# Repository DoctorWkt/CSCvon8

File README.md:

# CSCvon8: 8-bit von Neumann Crazy Small CPU

This repository holds the files for my 8-bit "big brother" CPU to the
[4-bit Crazy Small CPU](https://minnie.tuhs.org/Programs/CrazySmallCPU/).
This is a von Neumann style CPU designed with 7400-style logic chips, 32K of RAM, 32K of ROM and a UART. The CPU requires only seventeen chips, not including the
clock circuitry.
A short video is [here](https://www.youtube.com/watch?v=LJe3Z_fGDhg).

The overall design of the CPU is covered in
[Docs/CSCvon8_design.md](Docs/CSCvon8_design.md). Also read the
[getting started guide](Docs/getgoing_instructions.md) and the
[guide to building the PCB version](Docs/building_the_CSCvon8.md).

As at the 18th May 2019 I have the CPU running solidly at 3.57MHz on
the PCBs that I ordered from the PCB design in the Schematics folder.
I've kept a [journal](journal.md) with details of my progress from the
initial design phase through to the successful build.

The files and folders in this repository are:
- *Docs*, documents on the design and how to use the tools below
- *Examples*, example programs for the CPU
- *Schematic*, a KiCad schematic of the CPU
- *cas*, the assembler for the CPU
- *clc*, a very crude compiler that outputs assembly that can be given to cas
- *csim*, a simulator of the CPU written in Perl
- *disasm*, a tool to disassemble the instruction ROM contents
- *gen_alu*, a program to generate the contents of the ALU ROM
- *gen_ucode*, a program to generate the contents of the Decode ROM
- *journal.txt*, my running journal of the design and implementation of CSCvon8

There is also a Verilog version with the top-level file being
*ttlcsvon8.v*, the testbench is *icarus_tb.v* and the *Makefile* will
build and run the Verilog testbench. Some notes on this implementation
are in the
[*Docs/implementation_notes.md*](Docs/implementation_notes.md) file.

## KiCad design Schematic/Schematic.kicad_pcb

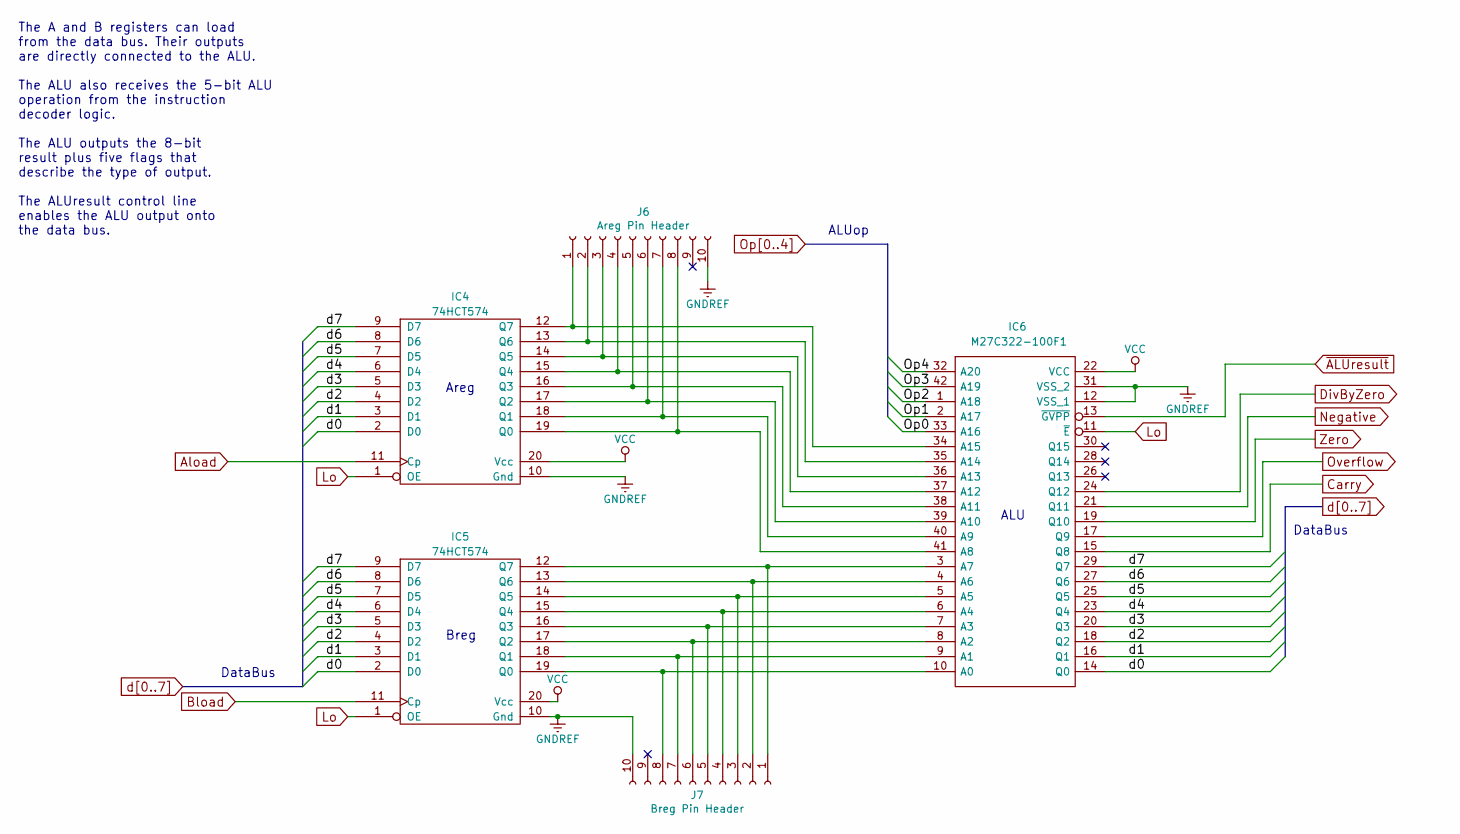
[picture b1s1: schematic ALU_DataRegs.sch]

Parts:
IC4, IC5: 74HCT574; DIP-20_W7.62mm_Socket
IC6: M27C322-100F1; DIP-42_W15.24mm_Socket; Manufacturer_Part_Number M27C322-100F1; Mouser Part Number 511-M27C322-10F
J6: Areg Pin Header; PinSocket_1x10_P2.54mm_Vertical
J7: Breg Pin Header; PinSocket_1x10_P2.54mm_Vertical

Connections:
Aload: IC4.11 (Cp); also elsewhere on the board
Bload: IC5.11 (Cp); also elsewhere on the board
Carry: IC6.15 (Q8); also elsewhere on the board
DivByZero: IC6.24 (Q12); also elsewhere on the board
Hi: IC4.20 (Vcc), IC5.20 (Vcc), IC6.22 (VCC); also elsewhere on the board
Negative: IC6.21 (Q11); also elsewhere on the board
unnamed: IC4.12 (Q7), IC6.34 (A15), J6.1
unnamed: IC4.13 (Q6), IC6.35 (A14), J6.2
unnamed: IC4.14 (Q5), IC6.36 (A13), J6.3
unnamed: IC4.15 (Q4), IC6.37 (A12), J6.4
unnamed: IC4.16 (Q3), IC6.38 (A11), J6.5
unnamed: IC4.17 (Q2), IC6.39 (A10), J6.6
unnamed: IC4.18 (Q1), IC6.40 (A9), J6.7
unnamed: IC4.19 (Q0), IC6.41 (A8), J6.8
unnamed: IC5.12 (Q7), IC6.3 (A7), J7.1
unnamed: IC5.13 (Q6), IC6.4 (A6), J7.2
unnamed: IC5.14 (Q5), IC6.5 (A5), J7.3
unnamed: IC5.15 (Q4), IC6.6 (A4), J7.4
unnamed: IC5.16 (Q3), IC6.7 (A3), J7.5
unnamed: IC5.17 (Q2), IC6.8 (A2), J7.6
unnamed: IC5.18 (Q1), IC6.9 (A1), J7.7
unnamed: IC5.19 (Q0), IC6.10 (A0), J7.8
Op0: IC6.33 (A16); also elsewhere on the board
Op1: IC6.2 (A17); also elsewhere on the board
Op2: IC6.1 (A18); also elsewhere on the board
Op3: IC6.42 (A19); also elsewhere on the board
Op4: IC6.32 (A20); also elsewhere on the board
Overflow: IC6.17 (Q9); also elsewhere on the board
Zero: IC6.19 (Q10); also elsewhere on the board
d0: IC4.2 (D0), IC5.2 (D0), IC6.14 (Q0); also elsewhere on the board
d1: IC4.3 (D1), IC5.3 (D1), IC6.16 (Q1); also elsewhere on the board
d2: IC4.4 (D2), IC5.4 (D2), IC6.18 (Q2); also elsewhere on the board
d3: IC4.5 (D3), IC5.5 (D3), IC6.20 (Q3); also elsewhere on the board
d4: IC4.6 (D4), IC5.6 (D4), IC6.23 (Q4); also elsewhere on the board
d5: IC4.7 (D5), IC5.7 (D5), IC6.25 (Q5); also elsewhere on the board
d6: IC4.8 (D6), IC5.8 (D6), IC6.27 (Q6); also elsewhere on the board
d7: IC4.9 (D7), IC5.9 (D7), IC6.29 (Q7); also elsewhere on the board
~ALUresult: IC6.13 (~GVPP); also elsewhere on the board

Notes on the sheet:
ALU
Areg
Breg
DataBus
ALUop
The A and B registers can load from the data bus. Their outputs are directly connected to the ALU. The ALU also receives the 5-bit ALU operation from the instruction decoder logic. The ALU outputs the 8-bit result plus five flags that describe the type of output. The ALUresult control line enables 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

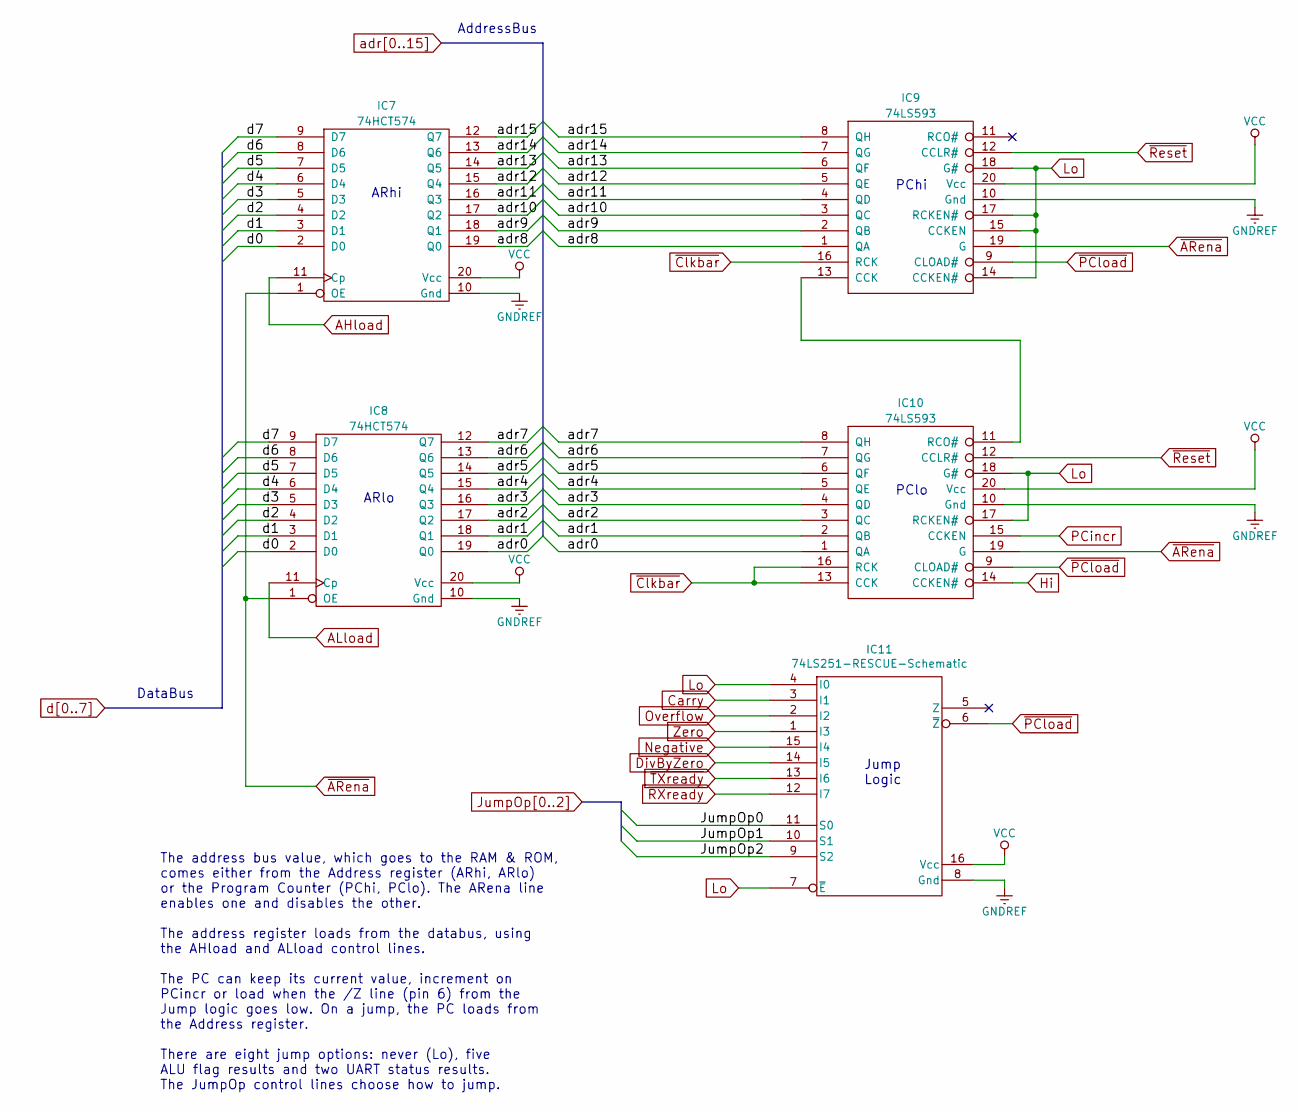
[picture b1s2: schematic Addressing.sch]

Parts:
IC7, IC8: 74HCT574; DIP-20_W7.62mm_Socket
IC9, IC10: 74LS593; DIP-20_W7.62mm_Socket
IC11: 74LS251-RESCUE-Schematic; DIP-16_W7.62mm_Socket

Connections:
AHload: IC7.11 (Cp); also elsewhere on the board
ALload: IC8.11 (Cp); also elsewhere on the board
Carry: IC11.3 (I1); also elsewhere on the board
DivByZero: IC11.14 (I5); also elsewhere on the board
Hi: IC7.20 (Vcc), IC8.20 (Vcc), IC9.20 (Vcc), IC10.14 (CCKEN#), IC10.20 (Vcc), IC11.16 (Vcc); also elsewhere on the board
JumpOp0: IC11.11 (S0); also elsewhere on the board
JumpOp1: IC11.10 (S1); also elsewhere on the board
JumpOp2: IC11.9 (S2); also elsewhere on the board
Negative: IC11.15 (I4); also elsewhere on the board
unnamed: IC9.13 (CCK), IC10.11 (RCO#)
Overflow: IC11.2 (I2); also elsewhere on the board
PCincr: IC10.15 (CCKEN); also elsewhere on the board
Zero: IC11.1 (I3); also elsewhere on the board
adr0: IC8.19 (Q0), IC10.1 (QA); also elsewhere on the board
adr1: IC8.18 (Q1), IC10.2 (QB); also elsewhere on the board
adr2: IC8.17 (Q2), IC10.3 (QC); also elsewhere on the board
adr3: IC8.16 (Q3), IC10.4 (QD); also elsewhere on the board
adr4: IC8.15 (Q4), IC10.5 (QE); also elsewhere on the board
adr5: IC8.14 (Q5), IC10.6 (QF); also elsewhere on the board
adr6: IC8.13 (Q6), IC10.7 (QG); also elsewhere on the board
adr7: IC8.12 (Q7), IC10.8 (QH); also elsewhere on the board
adr8: IC7.19 (Q0), IC9.1 (QA); also elsewhere on the board
adr9: IC7.18 (Q1), IC9.2 (QB); also elsewhere on the board
adr10: IC7.17 (Q2), IC9.3 (QC); also elsewhere on the board
adr11: IC7.16 (Q3), IC9.4 (QD); also elsewhere on the board
adr12: IC7.15 (Q4), IC9.5 (QE); also elsewhere on the board
adr13: IC7.14 (Q5), IC9.6 (QF); also elsewhere on the board
adr14: IC7.13 (Q6), IC9.7 (QG); also elsewhere on the board
adr15: IC7.12 (Q7), IC9.8 (QH); also elsewhere on the board
d0: IC7.2 (D0), IC8.2 (D0); also elsewhere on the board
d1: IC7.3 (D1), IC8.3 (D1); also elsewhere on the board
d2: IC7.4 (D2), IC8.4 (D2); also elsewhere on the board
d3: IC7.5 (D3), IC8.5 (D3); also elsewhere on the board
d4: IC7.6 (D4), IC8.6 (D4); also elsewhere on the board
d5: IC7.7 (D5), IC8.7 (D5); also elsewhere on the board
d6: IC7.8 (D6), IC8.8 (D6); also elsewhere on the board
d7: IC7.9 (D7), IC8.9 (D7); also elsewhere on the board
~ARena: IC7.1 (OE), IC8.1 (OE), IC9.19 (G), IC10.19 (G); also elsewhere on the board
~Clkbar: IC9.16 (RCK), IC10.13 (CCK), IC10.16 (RCK); also elsewhere on the board
~PCload: IC9.9 (CLOAD#), IC10.9 (CLOAD#), IC11.6 (~Z)
~RXready: IC11.12 (I7); also elsewhere on the board
~Reset: IC9.12 (CCLR#), IC10.12 (CCLR#); also elsewhere on the board
~TXready: IC11.13 (I6); also elsewhere on the board

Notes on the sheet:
Jump Logic
ARhi
ARlo
PChi
PClo
DataBus
AddressBus
The address bus value, which goes to the RAM & ROM, comes either from the Address register (ARhi, ARlo) or the Program Counter (PChi, PClo). The ARena line enables one and disables the other. The address register loads from the databus, using the AHload and ALload control lines. The PC can keep its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

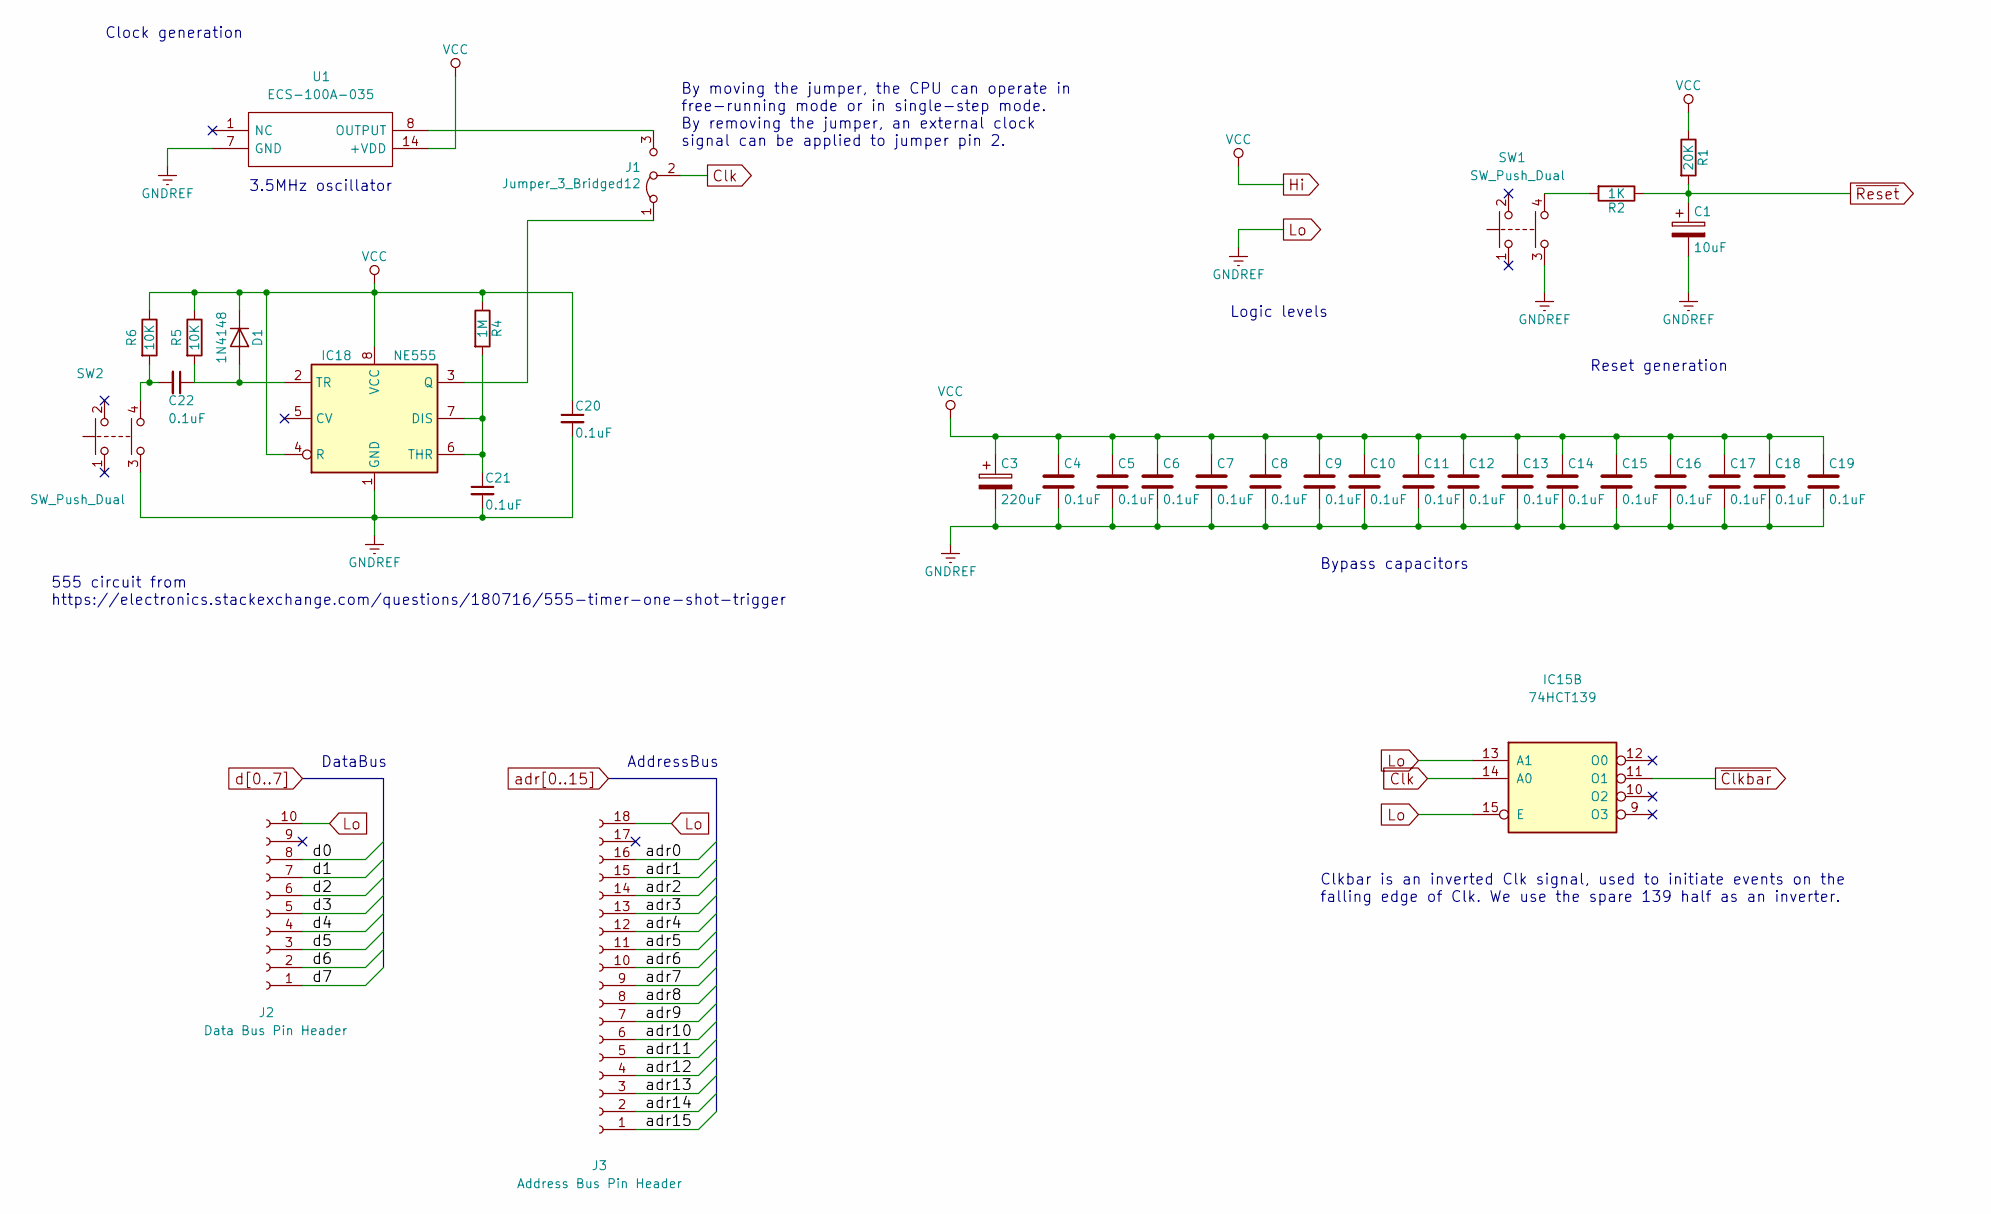
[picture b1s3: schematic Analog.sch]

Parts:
C1: 10uF; CP_Radial_D5.0mm_P2.00mm
C3: 220uF; CP_Radial_D8.0mm_P5.00mm
C4, C5, C6, C7, C8, C9, C10, C11, C12, C13, C14, C15, C16, C17, C18, C19, C20, C21, C22: 0.1uF; C_Disc_D4.7mm_W2.5mm_P5.00mm
D1: 1N4148; D_DO-35_SOD27_P2.54mm_Vertical_AnodeUp
IC15: 74HCT139; DIP-16_W7.62mm_Socket
IC18: NE555; DIP-8_W7.62mm_Socket
J1: Jumper_3_Bridged12; PinSocket_1x03_P2.54mm_Vertical
J2: Data Bus Pin Header; PinSocket_1x10_P2.54mm_Vertical
J3: Address Bus Pin Header; PinSocket_1x18_P2.54mm_Vertical
R1: 20K; R_Axial_DIN0204_L3.6mm_D1.6mm_P1.90mm_Vertical
R2: 1K; R_Axial_DIN0204_L3.6mm_D1.6mm_P1.90mm_Vertical
R4: 1M; R_Axial_DIN0204_L3.6mm_D1.6mm_P1.90mm_Vertical
R5, R6: 10K; R_Axial_DIN0204_L3.6mm_D1.6mm_P1.90mm_Vertical
SW1, SW2: SW_Push_Dual; Push_E-Switch_KS01Q01
U1: ECS-100A-035; QX14T50B1.843200B50TT; Manufacturer_Part_Number QX14T50B1.843200B50TT

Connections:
/Instruction Decode/DbusOp0: IC15.2 (A0); also elsewhere on the board
/Instruction Decode/DbusOp1: IC15.3 (A1); also elsewhere on the board
Hi: C3.1, C4.1, C5.1, C6.1, C7.1, C8.1, C9.1, C10.1, C11.1, C12.1, C13.1, C14.1, C15.1, C16.1, C17.1, C18.1, C19.1, C20.1, D1.1 (K), IC15.16 (VCC), IC18.4 (R), IC18.8 (VCC), R1.1, R4.1, R5.1, R6.1, U1.14 (+VDD); also elsewhere on the board
unnamed: C21.1, IC18.6 (THR), IC18.7 (DIS), R4.2
unnamed: C22.1, D1.2 (A), IC18.2 (TR), R5.2
unnamed: C22.2, R6.2, SW2.4
unnamed: IC18.3 (Q), J1.1 (A)
unnamed: J1.3 (B), U1.8 (OUTPUT)
unnamed: R2.2, SW1.4
adr0: J3.16; also elsewhere on the board
adr1: J3.15; also elsewhere on the board
adr2: J3.14; also elsewhere on the board
adr3: J3.13; also elsewhere on the board
adr4: J3.12; also elsewhere on the board
adr5: J3.11; also elsewhere on the board
adr6: J3.10; also elsewhere on the board
adr7: J3.9; also elsewhere on the board
adr8: J3.8; also elsewhere on the board
adr9: J3.7; also elsewhere on the board
adr10: J3.6; also elsewhere on the board
adr11: J3.5; also elsewhere on the board
adr12: J3.4; also elsewhere on the board
adr13: J3.3; also elsewhere on the board
adr14: J3.2; also elsewhere on the board
adr15: J3.1; also elsewhere on the board
d0: J2.8; also elsewhere on the board
d1: J2.7; also elsewhere on the board
d2: J2.6; also elsewhere on the board
d3: J2.5; also elsewhere on the board
d4: J2.4; also elsewhere on the board
d5: J2.3; also elsewhere on the board
d6: J2.2; also elsewhere on the board
d7: J2.1; also elsewhere on the board
~ALUresult: IC15.5 (O1); also elsewhere on the board
~Clkbar: IC15.11 (O1); also elsewhere on the board
~MEMresult: IC15.4 (O0); also elsewhere on the board
~Reset: C1.1, R1.2, R2.1; also elsewhere on the board
~UARTresult: IC15.6 (O2); also elsewhere on the board

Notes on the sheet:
By moving the jumper, the CPU can operate in free-running mode or in single-step mode. By removing the jumper, an external clock signal can be applied to jumper pin 2.
3.5MHz oscillator
Bypass capacitors
Reset generation
Clock generation
Logic levels
DataBus
AddressBus
555 circuit from https://electronics.stackexchange.com/questions/180716/555-timer-one-shot-trigger
Clkbar is an inverted Clk signal, used to initiate events on the falling edge of Clk. We use the spare 139 half as an inverter.

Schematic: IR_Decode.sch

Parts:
IC12: 74HCT574; DIP-20_W7.62mm_Socket
IC13: 74HCT161; DIP-16_W7.62mm_Socket
IC14: AT27C1024-70PU; DIP-40_W15.24mm_Socket; Manufacturer_Part_Number AT27C1024-70PU; Mouser Part Number 556-AT27C102470PU
IC15: 74HCT139; DIP-16_W7.62mm_Socket
IC16: 74HCT138; DIP-16_W7.62mm_Socket
IC17: 74LS04; DIP-14_W7.62mm_Socket
J4: uSeq Pin Header; Socket_Strip_Straight_1x06_Pitch2.54mm
J5: IR Pin Header; Socket_Strip_Straight_1x10_Pitch2.54mm

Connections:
/Instruction Decode/DbusOp0: IC14.10, IC15.2 (A0)
/Instruction Decode/DbusOp1: IC14.9, IC15.3 (A1)
/Instruction Decode/LoadOp0: IC14.14, IC16.1
/Instruction Decode/LoadOp1: IC14.13, IC16.2
/Instruction Decode/LoadOp2: IC14.12, IC16.3
AHload: IC17.8; also elsewhere on the board
ALload: IC17.10; also elsewhere on the board
Aload: IC17.4; also elsewhere on the board
Bload: IC17.6; also elsewhere on the board
Hi: IC12.20, IC13.7, IC13.10, IC13.16, IC14.1, IC14.39, IC14.40, IC15.16 (VCC), IC16.6, IC16.16, IC17.14 (VCC); also elsewhere on the board
IRload: IC12.11, IC17.2
JumpOp0: IC14.8; also elsewhere on the board
JumpOp1: IC14.7; also elsewhere on the board
JumpOp2: IC14.6; also elsewhere on the board
unnamed: IC12.12, IC14.33, J5.1
unnamed: IC12.13, IC14.32, J5.2
unnamed: IC12.14, IC14.31, J5.3
unnamed: IC12.15, IC14.29, J5.4
unnamed: IC12.16, IC14.28, J5.5
unnamed: IC12.17, IC14.27, J5.6
unnamed: IC12.18, IC14.26, J5.7
unnamed: IC12.19, IC14.25, J5.8
unnamed: IC13.11, IC14.24, J4.1
unnamed: IC13.12, IC14.23, J4.2
unnamed: IC13.13, IC14.22, J4.3
unnamed: IC13.14, IC14.21, J4.4
unnamed: IC16.9, IC17.11
unnamed: IC16.10, IC17.9
unnamed: IC16.12, IC17.5
unnamed: IC16.13, IC17.3
unnamed: IC16.14, IC17.1
Op0: IC14.19; also elsewhere on the board
Op1: IC14.18; also elsewhere on the board
Op2: IC14.17; also elsewhere on the board
Op3: IC14.16; also elsewhere on the board
Op4: IC14.15; also elsewhere on the board
PCincr: IC14.4; also elsewhere on the board
d0: IC12.2; also elsewhere on the board
d1: IC12.3; also elsewhere on the board
d2: IC12.4; also elsewhere on the board
d3: IC12.5; also elsewhere on the board
d4: IC12.6; also elsewhere on the board
d5: IC12.7; also elsewhere on the board
d6: IC12.8; also elsewhere on the board
d7: IC12.9; also elsewhere on the board
~ALUresult: IC15.5 (O1); also elsewhere on the board
~ARena: IC14.5; also elsewhere on the board
~IOload: IC16.7; also elsewhere on the board
~MEMload: IC16.11; also elsewhere on the board
~MEMresult: IC15.4 (O0); also elsewhere on the board
~Reset: IC13.1; also elsewhere on the board
~UARTresult: IC15.6 (O2); also elsewhere on the board
~uSreset: IC13.9, IC14.3

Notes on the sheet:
Decode ROM
uSequence Counter
Databus Writer demux
Databus Reader demux
DataBus
ALUop
CSCvon8 is a microsequenced CPU. The Instruction register, combined with the microsequence counter, selects the next microinstruction to perform. This is "looked up" in the Decode ROM, which produces the sixteen control lines for the specific microinstruction. The ALUop goes to the ALU. The JumpOp 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
It's so annoying that the 74HCT574 has an active high load line, and the RAM and UART have active low load lines. One extra chip just to deal with that, sigh.

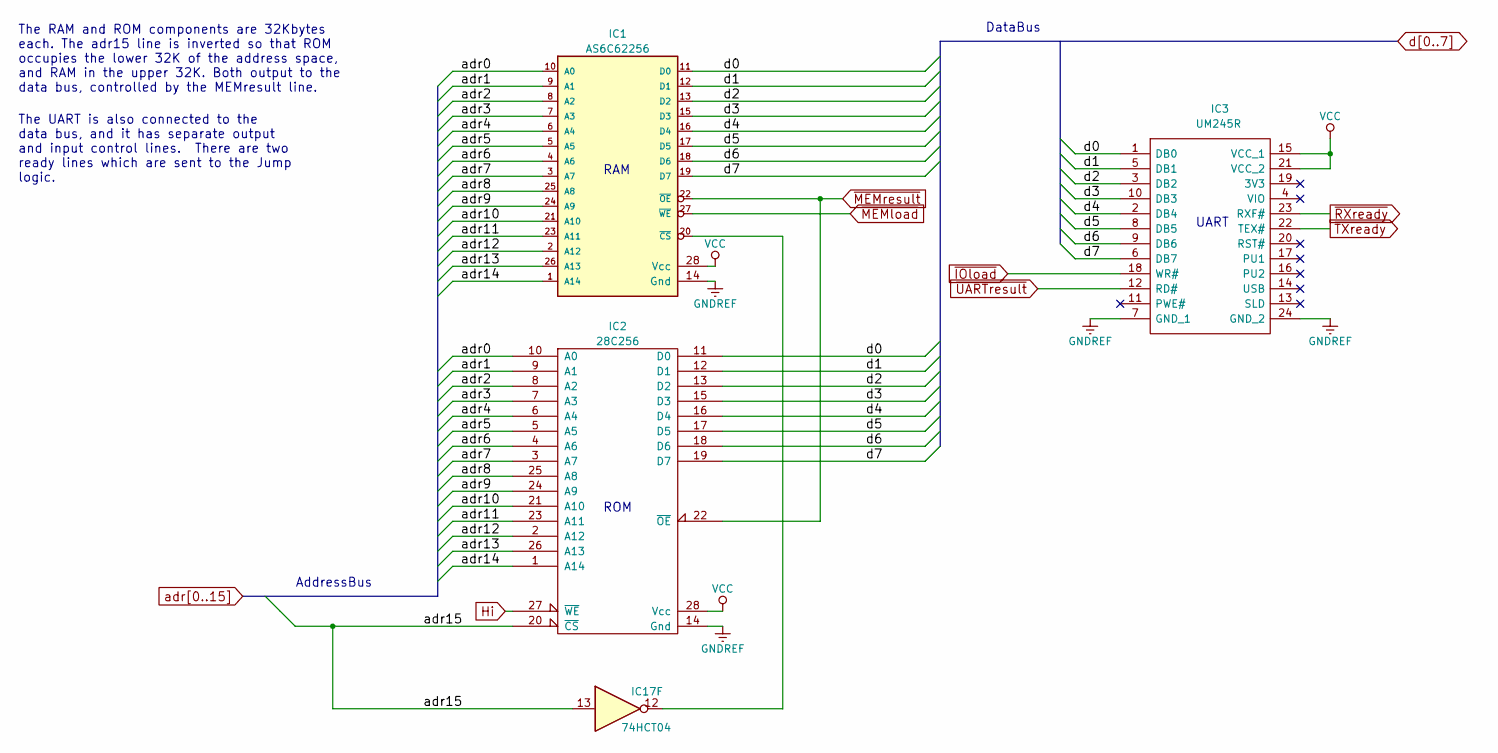
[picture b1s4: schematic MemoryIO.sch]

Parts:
IC1: AS6C62256; DIP-28_W15.24mm_Socket
IC2: 28C256; DIP-28_W15.24mm_Socket
IC3: UM245R; DIP-24_W15.24mm_Socket; Manufacturer_Part_Number UM245R; Mouser Part Number 895-UM245R
IC17: 74HCT04; DIP-14_W7.62mm_Socket

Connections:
AHload: IC17.8; also elsewhere on the board
ALload: IC17.10; also elsewhere on the board
Aload: IC17.4; also elsewhere on the board
Bload: IC17.6; also elsewhere on the board
Hi: IC1.28 (Vcc), IC2.27 (~WE), IC2.28 (Vcc), IC3.15 (VCC_1), IC3.21 (VCC_2), IC17.14 (VCC); also elsewhere on the board
IRload: IC17.2; also elsewhere on the board
unnamed: IC1.20 (~CS), IC17.12
unnamed 69: IC17.11; also elsewhere on the board
unnamed 70: IC17.9; also elsewhere on the board
unnamed 71: IC17.5; also elsewhere on the board
unnamed 72: IC17.3; also elsewhere on the board
unnamed 73: IC17.1; also elsewhere on the board
adr0: IC1.10 (A0), IC2.10 (A0); also elsewhere on the board
adr1: IC1.9 (A1), IC2.9 (A1); also elsewhere on the board
adr2: IC1.8 (A2), IC2.8 (A2); also elsewhere on the board
adr3: IC1.7 (A3), IC2.7 (A3); also elsewhere on the board
adr4: IC1.6 (A4), IC2.6 (A4); also elsewhere on the board
adr5: IC1.5 (A5), IC2.5 (A5); also elsewhere on the board
adr6: IC1.4 (A6), IC2.4 (A6); also elsewhere on the board
adr7: IC1.3 (A7), IC2.3 (A7); also elsewhere on the board
adr8: IC1.25 (A8), IC2.25 (A8); also elsewhere on the board
adr9: IC1.24 (A9), IC2.24 (A9); also elsewhere on the board
adr10: IC1.21 (A10), IC2.21 (A10); also elsewhere on the board
adr11: IC1.23 (A11), IC2.23 (A11); also elsewhere on the board
adr12: IC1.2 (A12), IC2.2 (A12); also elsewhere on the board
adr13: IC1.26 (A13), IC2.26 (A13); also elsewhere on the board
adr14: IC1.1 (A14), IC2.1 (A14); also elsewhere on the board
adr15: IC2.20 (~CS), IC17.13; also elsewhere on the board
d0: IC1.11 (D0), IC2.11 (D0), IC3.1 (DB0); also elsewhere on the board
d1: IC1.12 (D1), IC2.12 (D1), IC3.5 (DB1); also elsewhere on the board
d2: IC1.13 (D2), IC2.13 (D2), IC3.3 (DB2); also elsewhere on the board
d3: IC1.15 (D3), IC2.15 (D3), IC3.10 (DB3); also elsewhere on the board
d4: IC1.16 (D4), IC2.16 (D4), IC3.2 (DB4); also elsewhere on the board
d5: IC1.17 (D5), IC2.17 (D5), IC3.8 (DB5); also elsewhere on the board
d6: IC1.18 (D6), IC2.18 (D6), IC3.9 (DB6); also elsewhere on the board
d7: IC1.19 (D7), IC2.19 (D7), IC3.6 (DB7); also elsewhere on the board
~IOload: IC3.18 (WR#); also elsewhere on the board
~MEMload: IC1.27 (~WE); also elsewhere on the board
~MEMresult: IC1.22 (~OE), IC2.22 (~OE); also elsewhere on the board
~RXready: IC3.23 (RXF#); also elsewhere on the board
~TXready: IC3.22 (TEX#); also elsewhere on the board
~UARTresult: IC3.12 (RD#); also elsewhere on the board

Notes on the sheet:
RAM
ROM
UART
AddressBus
DataBus
The RAM and ROM components are 32Kbytes each. The adr15 line is inverted so that ROM occupies the lower 32K of the address space, and RAM in the upper 32K. Both output to the data bus, controlled by the MEMresult line.
The UART is also connected to the data bus, and it has separate output and input control lines. There are two ready lines which are sent to the Jump logic.

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
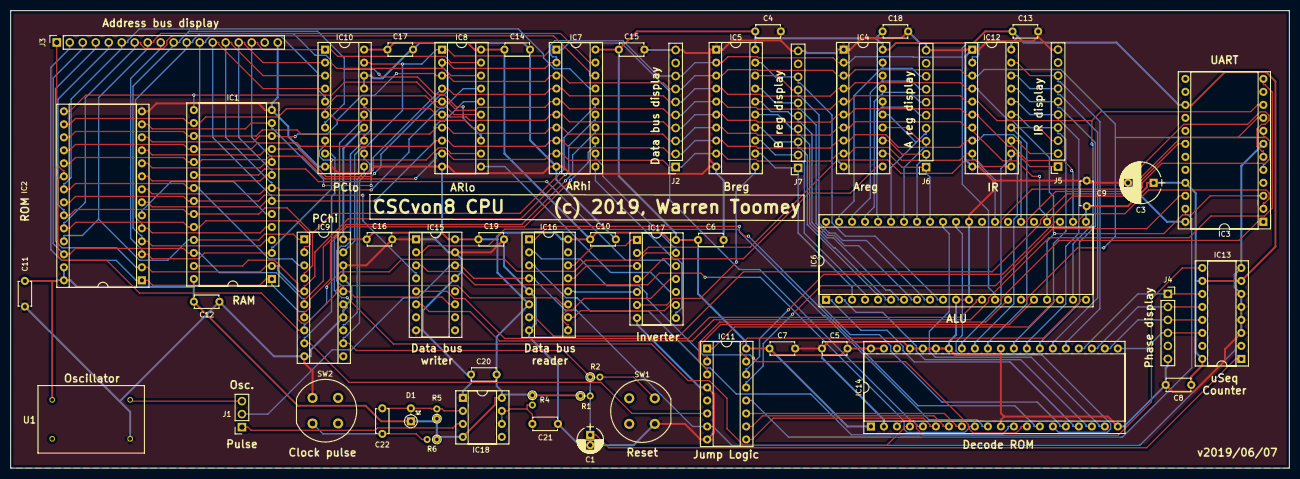
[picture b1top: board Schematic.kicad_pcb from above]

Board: 2 copper layers, 249.9 x 89.4 mm, 55 parts (0 on the bottom side), 104 nets.

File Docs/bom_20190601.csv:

Source:,/home/wkt/ownCloud/CSCvon8/Schematic/Schematic.sch,
Date:,Thu 09 May 2019 13:39:52 AEST,
Tool:,Eeschema 5.1.2-f72e74a~84~ubuntu18.04.1,
Component Count:,55,
,,
Ref,Value,Footprint
C1,10uF,Capacitors_THT:CP_Radial_D5.0mm_P2.00mm
C3,220uF,Capacitors_THT:CP_Radial_D8.0mm_P5.00mm
C4,0.1uF,Capacitors_THT:C_Disc_D4.7mm_W2.5mm_P5.00mm
C5,0.1uF,Capacitors_THT:C_Disc_D4.7mm_W2.5mm_P5.00mm
C6,0.1uF,Capacitors_THT:C_Disc_D4.7mm_W2.5mm_P5.00mm
C7,0.1uF,Capacitors_THT:C_Disc_D4.7mm_W2.5mm_P5.00mm
C8,0.1uF,Capacitors_THT:C_Disc_D4.7mm_W2.5mm_P5.00mm
C9,0.1uF,Capacitors_THT:C_Disc_D4.7mm_W2.5mm_P5.00mm
C10,0.1uF,Capacitors_THT:C_Disc_D4.7mm_W2.5mm_P5.00mm
C11,0.1uF,Capacitors_THT:C_Disc_D4.7mm_W2.5mm_P5.00mm
C12,0.1uF,Capacitors_THT:C_Disc_D4.7mm_W2.5mm_P5.00mm
C13,0.1uF,Capacitors_THT:C_Disc_D4.7mm_W2.5mm_P5.00mm
C14,0.1uF,Capacitors_THT:C_Disc_D4.7mm_W2.5mm_P5.00mm
C15,0.1uF,Capacitors_THT:C_Disc_D4.7mm_W2.5mm_P5.00mm
C16,0.1uF,Capacitors_THT:C_Disc_D4.7mm_W2.5mm_P5.00mm
C17,0.1uF,Capacitors_THT:C_Disc_D4.7mm_W2.5mm_P5.00mm
C18,0.1uF,Capacitors_THT:C_Disc_D4.7mm_W2.5mm_P5.00mm
C19,0.1uF,Capacitors_THT:C_Disc_D4.7mm_W2.5mm_P5.00mm
C20,0.1uF,Capacitors_THT:C_Disc_D4.7mm_W2.5mm_P5.00mm
C21,0.1uF,Capacitors_THT:C_Disc_D4.7mm_W2.5mm_P5.00mm
C22,0.1uF,Capacitors_THT:C_Disc_D4.7mm_W2.5mm_P5.00mm
D1,1N4148,Diodes_THT:D_DO-35_SOD27_P2.54mm_Vertical_AnodeUp
IC1,AS6C62256,Housings_DIP:DIP-28_W15.24mm_Socket
IC2,28C256,Housings_DIP:DIP-28_W15.24mm_Socket
IC3,UM245R,Housings_DIP:DIP-24_W15.24mm_Socket
IC4,74HCT574,Housings_DIP:DIP-20_W7.62mm_Socket
IC5,74HCT574,Housings_DIP:DIP-20_W7.62mm_Socket
IC6,M27C322-100F1,Housings_DIP:DIP-42_W15.24mm_Socket
IC7,74HCT574,Housings_DIP:DIP-20_W7.62mm_Socket
IC8,74HCT574,Housings_DIP:DIP-20_W7.62mm_Socket
IC9,74LS593,Housings_DIP:DIP-20_W7.62mm_Socket
IC10,74LS593,Housings_DIP:DIP-20_W7.62mm_Socket
IC11,74HCT151,Package_DIP:DIP-16_W7.62mm_Socket
IC12,74HCT574,Housings_DIP:DIP-20_W7.62mm_Socket
IC13,74HCT161,Housings_DIP:DIP-16_W7.62mm_Socket
IC14,AT27C1024-70PU,Housings_DIP:DIP-40_W15.24mm_Socket
IC15,74HCT139,Package_DIP:DIP-16_W7.62mm_Socket
IC16,74HCT138,Housings_DIP:DIP-16_W7.62mm_Socket
IC17,74HCT04,Housings_DIP:DIP-14_W7.62mm_Socket
IC18,NE555,Housings_DIP:DIP-8_W7.62mm_Socket
J1,Jumper_3_Bridged12,Connector_PinSocket_2.54mm:PinSocket_1x03_P2.54mm_Vertical
J2,Data Bus Pin Header,Connector_PinSocket_2.54mm:PinSocket_1x10_P2.54mm_Vertical
J3,Address Bus Pin Header,Connector_PinSocket_2.54mm:PinSocket_1x18_P2.54mm_Vertical
J4,uSeq Pin Header,Connector_PinSocket_2.54mm:PinSocket_1x06_P2.54mm_Vertical
J5,IR Pin Header,Connector_PinSocket_2.54mm:PinSocket_1x10_P2.54mm_Vertical
J6,Areg Pin Header,Connector_PinSocket_2.54mm:PinSocket_1x10_P2.54mm_Vertical
J7,Breg Pin Header,Connector_PinSocket_2.54mm:PinSocket_1x10_P2.54mm_Vertical
R1,20K,Resistors_THT:R_Axial_DIN0204_L3.6mm_D1.6mm_P1.90mm_Vertical
R2,1K,Resistors_THT:R_Axial_DIN0204_L3.6mm_D1.6mm_P1.90mm_Vertical
R4,1M,Resistors_THT:R_Axial_DIN0204_L3.6mm_D1.6mm_P1.90mm_Vertical
R5,10K,Resistors_THT:R_Axial_DIN0204_L3.6mm_D1.6mm_P1.90mm_Vertical
R6,10K,Resistors_THT:R_Axial_DIN0204_L3.6mm_D1.6mm_P1.90mm_Vertical
SW1,SW_Push_Dual,Buttons_Switches_THT:Push_E-Switch_KS01Q01
SW2,SW_Push_Dual,Buttons_Switches_THT:Push_E-Switch_KS01Q01
U1,ECS-100A-035,QX14T50B1.843200B50TT:QX14T50B1.843200B50TT

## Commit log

2019-03-27 First version ready for exposure on Github.
2019-03-27 Broken link in README
2019-03-27 Oops, missed one Verilog source file
2019-03-27 Fixed up some schematic DCN mistakes and also a few minor typos and diagram issues.
2019-03-27 Generated a new schematic of the circuit
2019-03-27 Brought design document up to date with new order of ALU flags lines.
2019-03-27 Working on the PCB
2019-03-28 Added a reset circuit and a single-step clock circuit to the schematic, as well as the bypass capacitors. Also, got used to the PCB creation workflow.
2019-03-28 Brought in support for Verilator
2019-04-23 Brought the schematic and PCB board design up to date.
2019-04-23 Added the Verilog version of the CPU which is composed of models of the TTL components which I will use to build the CPU.
2019-04-23 Tidy up of the docs
2019-04-23 Brought my journal up to date.
2019-04-23 Brought in the new assembler, compiler and other tools that I've been working on.
2019-04-23 Brought the example assembly files up to date with the new assembler.
2019-04-23 Still bringing things up to date. Top Makefile now makes the ALU and microcode ROM contents.
2019-04-23 I've removed the original Verilog version and now have just the TTL Verilog version of the CPU along with the Perl simulator.
2019-04-24 Updated the diagrams of the design.
2019-04-24 Updated the top-level README file
2019-04-24 Updated the get started instructions.
2019-04-24 Updated the design document
2019-04-24 Moved some documentation into the Docs folder.
2019-04-24 Updated the cas assembler manual
2019-04-24 Fixed up some mistakes in the docs.
2019-04-24 Got the CCK enable logic a bit wrong cf. the real chips, so fixed it.
2019-04-25 I missed some control lines to the ROM and then had to fix up a microsequence.
2019-04-25 Brought the schematic up to date with the wiring from the TTL verilog version.
2019-04-25 Moved the Figs into Docs and brought the implementation notes up to date.
2019-04-25 The rewiring of the TTL verilog version has forced an increase in the minimum clock cycle duration.
2019-04-25 Journal entry.
2019-04-25 Going to move the journal to Markdown.
2019-04-25 Got rid of the old text journal.
2019-04-25 More journal notes.
2019-04-25 Updated journal after a bit of a struggle loading the PC.
2019-04-25 More journal entries.
2019-04-26 Updated my 74593 wiring as per my journal notes from last night.
2019-04-26 Reworked the 74LS593 wiring in the KiCad schematic and updated my journal.
2019-04-26 Included a photo of the breadboard in the journal.
2019-04-26 gen_ucode now shows the hex version of each microinstruction with -d
2019-04-26 Updated the PC_circuit.png in the documentation.
2019-04-27 Updated journal, I now have an Instruction ROM and a data bus.
2019-04-28 I wired up some of the A-register and the UART to write from the data bus. I've added an OUT instruction to output the next byte after the instruction byte. I've written a short test program and this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
2019-04-28 Journal update.
2019-04-28 I added a NOP to the start of the example programs, as the hardware doesn't properly run the instruction at $0000 after a reset.
2019-04-28 Fixed some mistakes in the chips and the details of the design.
2019-05-02 Brought the journal up to date
2019-05-02 New image.
2019-05-03 I added the SIA/SIB instructions and had to change a few programs to deal with this. There is an Examples/example10.s program which uses these instructions. Updated the journal too.
2019-05-04 Updated journal.
2019-05-04 Another journal update with a new picture.
2019-05-04 Fixed a bug with the PC incrementing incorrectly.
2019-05-05 I now have a working CPU on the breadboard.
2019-05-05 Journal typos fixed.
2019-05-05 More types fixed!
2019-05-05 Yet another typo corrected.
2019-05-06 Updated the schematic and also moved to KiCad 5.
2019-05-08 Brought the PCB up to date with the new schematic, and tested the RAM with a test program.
2019-05-08 Added -r: randomise RAM to csim, updated my journal.
2019-05-08 I've updated the schematic PDF from the latest KiCad design.
2019-05-08 Updated the PCB image and my journal.
2019-05-09 I forgot the image!
2019-05-09 Typo in journal.
2019-05-09 Updated the README with details of progress.
2019-05-11 Brought the implementation notes up to date with the new PC circuit.
2019-05-13 Some more rewording of the documentation.
2019-05-16 The PCBs have turned up and I'm getting on with the soldering.
2019-05-17 First working instructions on the PCB.
2019-05-17 The PCB is nearly finished, only a few chips left to add. Works so far.
2019-05-17 More journal notes
2019-05-17 A new photo of a working CPU.
2019-05-18 Runs fine a 1MHz.
2019-05-18 Found a workaround to fix the bug in the Jump instructions.
2019-05-18 Improved the microcode and kept the CPU running OK at 3.57MHz.
2019-05-18 Added numeric labels with relative references to the assembler.
2019-05-19 Removed a control line from the microcode to get the LIA and LIB instructions to work on the real hardware.
2019-05-19 Added support for label+num syntax to the assembler.
2019-05-22 Added ; support to cas so I can set up some cpp macros. Updated the journal. I've undone some of the LDA JC style changes because of the side effects of calculating A-1, A+1, B+1 A+B etc. multiple ti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
2019-05-25 I've spent some time shaking out some annoying microcode bugs.
2019-05-25 Added an introduction to the journal.
2019-05-25 Some more updates to the documentation.
2019-05-25 Updated the PCB so that the UM245R has the correct physical orientation with the USB port facing the edge of the PCB.
2019-05-27 I put in a hard-coded UART input value so I can do some sort of INA and INB testing.
2019-05-28 I added support in cas to assemble into RAM and generate a RAM hex file which can be loaded with the monitor.
2019-05-29 I've added one more instruction to the instruction set.
2019-05-30 Added a version of Conway's Game of Life as an example.
2019-05-30 Fix up wktlife.s to clear RAM before it starts.
2019-05-31 Updated the examples to use the current set of instructions.
2019-05-31 Updated the PCB and schematic to have a 330pF capacitor to fix the "jump" glitch that I've been experiencing.
2019-05-31 Brought the journal up to date.
2019-05-31 I finally added the Monitor ROM code, now that it's stable.
2019-05-31 Changed the version number on the PCB to reflect the new capacitor.
2019-05-31 Added a Misc folder in my dev repo.
2019-06-01 I've made a start on a document that describes how to build and test the CSCvon8 CPU on the PCB, in stages.
2019-06-01 I've mostly completed the "building_the_CSCvon8" documentation but there are new small things to add.
2019-06-01 Fixed up some URLs in building_the_CSCvon8.md
2019-06-01 Fixed some more mistakes in building_the_CSCvon8.md
2019-06-01 Added a link to Docs/building_the_CSCvon8.md to the README.
2019-06-01 typo in building_the_CSCvon8.md
2019-06-01 Center the images in building_the_CSCvon8.md
2019-06-01 Removed the centering, didn't work!
2019-06-02 I think I've mostly finished the building_the_CSCvon8.md document except for any typos.
2019-06-02 A better image of the UM245R.
2019-06-02 Found some typos and mistakes in building_the_CSCvon8.md, fixed.
2019-06-02 Added link to the video to the README.md.
2019-06-02 Added a photo of the "glitch" reducing capacitor.
2019-06-02 Added the picture as well.
2019-06-05 I've added the scripts that I use to burn the ROMs. I've added a new example program, ttt.s, which plays Tic Tac Toe (Noughts and Crosses). I've added a new instruction to the instruction set, and I'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
2019-06-06 Updated the journal with details of the new logic analyser and the glitch capacitor.
2019-06-06 I just realised that a 74HCT151 should fix the jump glitch.
2019-06-07 I'm using a 74HCT151 and the jump glitch is gone!
2019-06-07 I've updated the microcode to have the jump instructions with shorter microsequences. They all seem to work with the 74HCT151. The hardware is now officially "solid".
2019-06-07 I've updated the Verilog version of the CPU, and the documentation, to reflect the change to the 74HCT151 chip.
    The PCB hasn't yet been changed, but that's coming soon.
2019-06-07 I've updated the schematic and the PCB to have the 74HCT151 chip.
2019-06-07 Added an image of the 20190607 board to the build notes.
2019-06-08 Updated the documentation for the assembler.
2019-06-08 Fixed up the assembler docs a bit more.
2019-06-08 New journal entry.
2019-06-08 We no longer need the 'Old' folder.
2019-06-09 Another journal update.
2019-06-25 Changed the 1st pic in the README.
2019-09-14 More details on RAM & ROM
2020-05-07 Fix misordered ALU operations in table

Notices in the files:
Schematic/Schematic.kicad_pcb:
CSCvon8 CPU (c) 2019, Warren Toomey
